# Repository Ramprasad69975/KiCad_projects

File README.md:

# 🚀 KiCad PCB Design Playground

Hello everyone! 👋  
Welcome to my KiCad PCB design repository — this is where I turn circuit ideas into real PCB layouts.

This repository is a collection of my **PCB design projects, experiments, and learning journey** using KiCad. You’ll find schematics, board layouts, and Gerber files as I explore both analog and digital circuit design.

---

## 🔧 What’s Inside

This repo contains:

- 📐 PCB schematics and layouts  
- ⚡ Analog and digital circuit designs  
- 🧪 Learning experiments and test boards  
- 📦 Manufacturing-ready Gerber files  
- 🧠 Design notes and improvements over time  

---

## 🎯 Purpose of This Repository

I created this repository to:

- Practice real-world PCB design skills  
- Document my learning progress  
- Build a public hardware portfolio  
- Share designs for learning and collaboration  
- Improve layout, routing, and design thinking  

---

## 🛠 Tools Used

- **KiCad** for schematic capture and PCB layout  
- Basic electronic design principles  
- Trial, error, and iteration 😄  

---

## 📈 What You Can Expect

I’ll be adding:

- Beginner PCBs (learning layouts)  
- Functional modules (power, drivers, controllers)  
- More optimized designs as I grow  
- Design revisions and improvements  

---

## 🤝 Contributions & Feedback

If you have suggestions, corrections, or ideas, feel free to open an issue or share feedback.  
I’m here to learn and improve!

---

## 🏁 Author

Maintained by **Ramprasad**

---

Stay tuned for more designs and updates ⚡

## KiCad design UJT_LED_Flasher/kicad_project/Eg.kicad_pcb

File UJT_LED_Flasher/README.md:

# UJT LED Flasher PCB

This is a KiCad PCB design for a UJT-based LED flasher (relaxation oscillator).

---

## 📁 Project Structure

```text
UJT_LED_Flasher/
├── kicad_project/   → Original KiCad design files
├── schematic/       → Circuit diagram image(s)
├── pcb_layout/      → Top, bottom, and 3D PCB view images
├── gerber_files/    → Manufacturing-ready Gerber files
└── README.md        → Project description (this file)

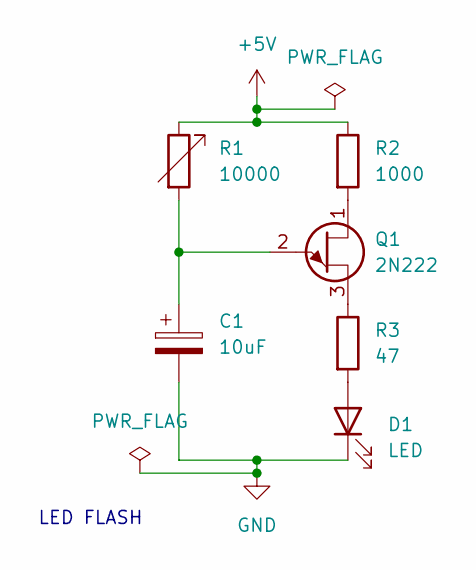
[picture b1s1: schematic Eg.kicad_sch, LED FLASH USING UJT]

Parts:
C1: 10uF; CP_Axial_L18.0mm_D6.5mm_P25.00mm_Horizontal
D1: LED; LED_D5.0mm
Q1: 2N222; TO-92
R1: 10000; R_Axial_DIN0207_L6.3mm_D2.5mm_P7.62mm_Horizontal
R2: 1000; R_Axial_DIN0207_L6.3mm_D2.5mm_P10.16mm_Horizontal
R3: 47; R_Axial_DIN0207_L6.3mm_D2.5mm_P10.16mm_Horizontal

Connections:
+5V: R1.1, R2.1
GND: C1.2, D1.1 (K)
unnamed: D1.2 (A), R3.2
unnamed: Q1.3 (B1), R3.1
unnamed: Q1.1 (B2), R2.2
unnamed: C1.1, Q1.2 (E), R1.2

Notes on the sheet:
LED FLASH

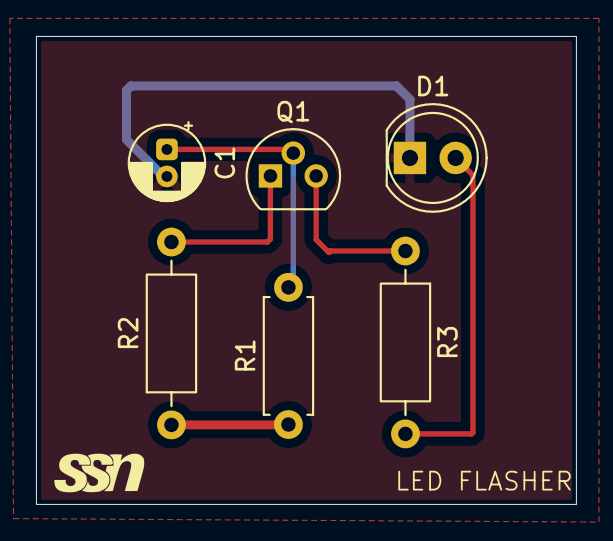
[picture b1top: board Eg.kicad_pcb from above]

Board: 2 copper layers, 30.0 x 26.0 mm, 6 parts (0 on the bottom side), 6 nets.

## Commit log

2025-12-02 Revise README for UJT LED Flasher PCB project
    Updated README to include details about UJT LED flasher PCB design project, including project overview, working principle, components used, design tools, repository contents, PCB views, features, and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
2025-12-02 Enhance README with project details and structure
    Expanded README to provide detailed information about the KiCad PCB design repository, including its purpose, contents, tools used, and expectations.
2025-12-02 Update author name from Rapo to Ramprasad
2025-12-02 Add README for UJT LED Flasher project
2025-12-02 Add .gitkeep to kicad_project directory
    Add placeholder file to keep kicad_project directory in Git
2025-12-02 Create schematic folder for UJT LED flasher
2025-12-02 Add .gitkeep file to kicad_project directory
2025-12-02 Add .gitkeep to schematic directory
2025-12-02 Add .gitkeep to pcb_layout directory
2025-12-02 Add .gitkeep to gerber_files directory
    Create a placeholder file to keep the gerber_files directory in the repository.
2025-12-02 Add files via upload
    Add KiCad project files for UJT LED flasher
2025-12-02 Add files via upload
    Add Gerber files for UJT LED flasher PCB
2025-12-02 Update README with project details and structure
    Expanded project description and added project structure details.
2025-12-02 Remove file
